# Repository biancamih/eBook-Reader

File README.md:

# OpenBook 
**Autor: Mihai Bianca-Ioana**

## Diagrama Bloc
```
                            +------------------------+
                            | USB-C Connector & ESD  |
                            +------------------------+
                                      |
                                      v
                             +------------------+
                             |   LDO Regulator   |
                             +------------------+
                                      |
                                      v
 +-------------------+       +------------------+       +---------------------+
 | Li-Po Charging IC | ----> | ESP32-C6 WROOM-1 | <-->  |    SD Card          |
 +-------------------+       +------------------+       +---------------------+
                                      |  ^   ^  ^
                                      |  |   |  |
         +------------------+         |  |   |  +---------------------+
         | Environmental     | -------+  |   +----------------+       |
         | Sensor (BME688)   |            |                    |       |
         +------------------+            |  +--------------+  |       |
                                         +->| NOR Flash     |<-+       |
                                         |  +--------------+          |
                                         |                             |
             +---------------+           +->| Battery Gauge |          |
             |   E-Paper     |<--------------+ (MAX17048)   |          |
             |   Driver      |           |  +---------------+          |
             +---------------+           |                             |
                                         +->| RTC (DS3231)  |<---------+
                                         |
                                         +->| Buttons       |
                                            +---------------+
```

## Bill Of  Materials (BOM)
| Component Name                            | Link                                                                                                   | Datasheet Link                                                                                           |
|------------------------------------------|-------------------------------------------------------------------------------------------------------------|-----------------------------------------------------------------------------------------------------------|
| 112ATAARR03ATTEND                        | [Link](https://store.comet.srl.ro/Catalogue/Product/43497/)                                                | [Link](https://www.attend.com.tw/data/download/file/112A-TAAR-R03.rar)                                   |
| ADAFRUIT_CHIP-LED0603                    | [Link](https://www.snapeda.com/parts/KP-1608SURCK/Kingbright/view-part/?ref=search&t=LED%200603)           | [Link](https://www.snapeda.com/parts/KP-1608SURCK/Kingbright/datasheet/)                                 |
| CAPCP3225X100N                           | [Link](https://www.snapeda.com/parts/CPH3225A/Seiko+Instruments/view-part/?ref=eda)                        | [Link](https://www.snapeda.com/parts/CPH3225A/Seiko%20Instruments/datasheet/)                            |
| DIOC1608X36N                             | [Link](https://www.snapeda.com/parts/PGB1010603MR/Littelfuse/view-part/?ref=eda)                           | [Link](https://www.snapeda.com/parts/PGB1010603MR/Littelfuse%20Inc./datasheet/)                          |
| EAGLE-LTSPICE_C0402                      | [Link](https://componentsearchengine.com/part-view/CC0402MRX5R5BB106/YAGEO)                                 | [Link](https://componentsearchengine.com/Datasheets/2/CC0402MRX5R5BB106.pdf)                              |
| ESP32_WROVER_AVX---SD0805S020S1R0_AVX_0  | [Link](https://ro.mouser.com/ProductDetail/KYOCERA-AVX/SD0805S020S1R0?qs=jCA%252BPfw4LHbpkAoSnwrdjw%3D%3D) | [Link](https://ro.mouser.com/datasheet/2/40/schottky-3165252.pdf)                                        |
| ESP32_WROVER_BME680_PSON80P300X300X100-8N| [Link](https://www.snapeda.com/parts/BME680/Bosch/view-part/?welcome=home)                                 | [Link](https://www.snapeda.com/parts/BME680/Bosch%20Sensortec/datasheet/)                                |
| ESP32_WROVER_EAGLE-LTSPICE_C0402         | [Link](https://componentsearchengine.com/part-view/CC0402MRX5R5BB106/YAGEO)                                 | [Link](https://componentsearchengine.com/Datasheets/2/CC0402MRX5R5BB106.pdf)                              |
| ESP32_WROVER_EAGLE-LTSPICE_R0402         | [Link](https://componentsearchengine.com/part-view/R0402%201%25%20100%20K%20(RC0402FR-07100KL)/YAGEO)       | [Link](https://www.yageo.com/upload/media/product/products/datasheet/rchip/PYu-RC_Group_51_RoHS_L_12.pdf)|
| ESP32_WROVER_SPARKFUN-DISCRETESEMI_SOT23-3| [Link](https://componentsearchengine.com/part-view/DMG2305UX-7/Diodes%20Incorporated)                      | [Link](https://www.diodes.com//assets/Datasheets/DMG2305UX.pdf)                                          |
| ESP32_WROVER_SPARKFUN-IC-POWER_SOT23-5   | [Link](https://ro.mouser.com/ProductDetail/Microchip-Technology/MCP73831T-5ACI-OT?qs=hH%252BOa0VZEiAcgAcEkuamXg%3D%3D) | [Link](https://ro.mouser.com/datasheet/2/268/MCP73831_Family_Data_Sheet_DS20001984H-3441711.pdf)         |
| ESP32C6_VARISTOR_CT/CN1812               | [Link](https://ro.mouser.com/ProductDetail/EPCOS-TDK/B72520T0350K062?qs=dEfas%2FXlABIszF52uu7vrg%3D%3D)     | [Link](https://www.tdk-electronics.tdk.com/inf/75/db/CTVS_14/Surge_protection_series.pdf)                |
| FH34SRJ24S05SH99                         | [Link](https://ro.mouser.com/ProductDetail/Hirose-Connector/FH34SRJ-24S-0.5SH99?qs=vcbW%252B4%252BSTIpKBl5ap9J8Fw%3D%3D) | [Link](https://ro.mouser.com/datasheet/2/185/FH34SRJ_24S_0_5SH_99__CL0580_1255_6_99_2DDrawing_0-1615044.pdf)|
| IND_4828-WE-TPC_WRE                      | [Link](https://ro.mouser.com/ProductDetail/Wurth-Elektronik/744043680?qs=PGXP4M47uW6VkZq%252BkzjrHA%3D%3D)  | [Link](https://www.we-online.com/components/products/datasheet/744043680.pdf)                            |
| JST04_1MM_RA                             | [Link](https://ro.mouser.com/ProductDetail/Adafruit/4208?qs=PzGy0jfpSMtbScLbr0L5dw%3D%3D)                   | [Link](https://ro.mouser.com/ProductDetail/Adafruit/4208?qs=PzGy0jfpSMtbScLbr0L5dw%3D%3D)                 |
| MYBUTTON                                 | [Link](https://industry.panasonic.com/global/en/products/control/switch/light-touch/number/evqpuj02k)      | [Link](https://industry.panasonic.com/global/en/downloads?tab=catalog&small_g_cd=203&part_no=EVQPUJ02K)  |
| RCL_CT3528                               | [Link](https://www.snapeda.com/parts/TAJB475K025RNJ/AVX/view-part/?t=capacitor%203528&con_ref=None)        | [Link](https://www.snapeda.com/parts/TAJB475K025RNJ/AVX/datasheet/)                                      |
| SAMACSYS_PARTS_USB4110GFA                | [Link](https://componentsearchengine.com/part-view/USB4110-GF-A/GCT%20(GLOBAL%20CONNECTOR%20TECHNOLOGY))   | [Link](https://gct.co/files/drawings/usb4110.pdf)                                                         |
| SOD3716X135N                             | [Link](https://ro.mouser.com/ProductDetail/KYOCERA-AVX/SD0805S020S1R0?qs=jCA%252BPfw4LHbpkAoSnwrdjw%3D%3D) | [Link](https://ro.mouser.com/datasheet/2/40/schottky-3165252.pdf)                                        |
| SOIC127P1032X265-16N                     | [Link](https://eu.mouser.com/ProductDetail/Wurth-Elektronik/744043680?qs=PGXP4M47uW6VkZq%252BkzjrHA%3D%3D)  | [Link](https://www.snapeda.com/parts/DS3231SN%23/Analog%20Devices/datasheet/)                            |
| SON127P600X800X80-9N                     | [Link](https://www.snapeda.com/parts/W25Q512JVEIQ/Winbond+Electronics/view-part/?ref=eda)                 | [Link](https://www.snapeda.com/parts/W25Q512JVEIQ/Winbond%20Electronics/datasheet/)                      |
| SON50P200X200X80-9N                      | [Link](https://www.snapeda.com/parts/MAX17048G+T10/Analog+Devices/view-part/?ref=eda)                      | [Link](https://www.snapeda.com/parts/MAX17048G+T10/Analog%20Devices/datasheet/)                          |
| SOT65P210X110-3N                         | [Link](https://componentsearchengine.com/part-view/SI1308EDL-T1-GE3/Vishay)                                 | [Link](https://componentsearchengine.com/Datasheets/1/SI1308EDL-T1-GE3.pdf)                               |
| SOT95P280X125-5N                         | [Link](https://componentsearchengine.com/part-view/BD5229G-TR/ROHM%20Semiconductor)                         | [Link](https://datasheet.datasheetarchive.com/originals/distributors/Datasheets_SAMA/f2b9741ef86007909f138d561a359946.pdf) |
| SOT95P280X145-6N                         | [Link](https://www.snapeda.com/parts/USBLC6-2SC6Y/STMicroelectronics/view-part/?ref=eda)                   | [Link](https://www.snapeda.com/parts/USBLC6-2SC6Y/STMicroelectronics/datasheet/)                         |
| XCVR_ESP32-C6-WROOM-1-N8                 | [Link](https://www.snapeda.com/parts/ESP32-C6-WROOM-1-N8/Espressif+Systems/view-part/?ref=eda)             | [Link](https://www.snapeda.com/parts/ESP32-C6-WROOM-1-N8/Espressif%20Systems/datasheet/)                 |

## Descriere functionala hardware 

###  Arhitectura Hardware

Sistemul este bazat pe microcontrollerul **ESP32-C6-WROOM-1**, cu conectivitate Wi-Fi 6 și BLE, gândit pentru funcționare autonomă și consum redus de energie. Dispozitivul este alimentat de la o baterie Li-Po și poate fi programat prin USB-C. Componentele sunt interconectate prin SPI, I2C și GPIO.

---

### Alimentare și management baterie

- **USB-C Connector & ESD Protection**  
  Conector: `USB4110-GF-A`  
  Protecție ESD: `USBLC6-2SC6Y`

- **LDO Voltage Regulator**  
  Asigură 3.3V stabil pentru întreaga placă

- **Li-Po Battery Charger**  
  MCP73831 – circuit dedicat pentru încărcarea bateriei

- **Battery Gauge (MAX17048)**  
  Măsoară nivelul bateriei și comunică prin I2C

---

### Microcontroller principal

- **ESP32-C6-WROOM-1-N8**  
  RISC-V MCU cu Wi-Fi 6, BLE, 8MB flash intern  
  Rol: control central, comunicare cu senzori, logare, afișare

---

### Stocare

- **SD Card** – pentru loguri de date, firmware, fișiere
- **W25Q512 NOR Flash** – pentru memorie suplimentară SPI (64Mbit)

---

### Senzori & Ceas

- **BME688** – măsoară temperatură, umiditate, presiune și gaze (I2C)
- **DS3231** – ceas de timp real, cu precizie ridicată (I2C)

---

### Afișaj

- **E-Paper Driver + Conector**  
  Conectat prin SPI, controlat de ESP32  
  Alimentarea este comutabilă cu un MOSFET (SI1308EDL)

---

### Control și testare

- **Reset / Boot Buttons**
- **Qwiic/Stemma QT Connector** – extensii I2C
- **Test Pads** – debugging ușor

---

### Protecții

- **TVS Diodes**: `PGB1010603MR` – protecție ESD pe linii sensibile
- **Varistori**: protecție la supratensiuni

---

### Conexiuni interfețe

| Interfață | Dispozitive conectate                          |
|-----------|------------------------------------------------|
| I2C       | BME688, DS3231, MAX17048                       |
| SPI       | SD Card, NOR Flash, E-Paper Display            |
| GPIO      | Butoane, LED-uri, Power switches               |

## Estimare Consum Energie

| Componentă                  | Mod activ (mA) | Standby (mA) | Deep sleep (µA) | Observații                                 |
|----------------------------|----------------|--------------|-----------------|--------------------------------------------|
| **ESP32-C6**               | 50–80          | ~2           | ~5              | Wi-Fi consumă cel mai mult                 |
| **BME688**                 | 2.1            | 0.15         | <1              | Măsurare la 1Hz                            |
| **DS3231 (RTC)**           | 0.15           | 0.15         | 0.15            | Activ permanent                            |
| **MAX17048 (Battery Gauge)**| 0.06          | 0.006        | 0.006           | Foarte eficient                            |
| **E-paper Display**        | 5–20           | 0            | 0               | Consumă doar în timpul refresh-ului        |
| **SD Card (scriere activă)**| 30–100        | 0.2          | 0               | Alimentat doar la nevoie                   |
| **W25Q512 (SPI Flash)**    | ~5             | 0.003        | <1              | Are mod standby foarte eficient            |
| **LDO Regulator + pierderi**| 2–5           | 0.5          | 0.2             | Inclus în consum general                   |

---

##  Mapare pini ESP32-C6 

| Pin ESP32-C6 | Componentă                     | Funcție/Interfață     | Motiv / Utilizare                                                                 |
|--------------|-------------------------------|------------------------|-----------------------------------------------------------------------------------|
| **IO0**      | Buton `BOOT`                  | GPIO / Input          | Intrare folosită pentru intrarea în mod bootloader                               |
| **IO1**      | `RTC DS3231`                  | I2C SDA               | Comunicare cu ceasul de timp real                                                |
| **IO2**      | `RTC DS3231`                  | I2C SCL               | Comunicare I2C                                                                    |
| **IO3**      | `BME688`, `MAX17048`          | I2C SDA               | Magistrală I2C partajată cu ceilalți senzori                                     |
| **IO4**      | `BME688`, `MAX17048`          | I2C SCL               |                                                                                   |
| **IO5**      | `W25Q512 NOR Flash`           | SPI CS                | Chip select pentru memoria flash externă                                         |
| **IO6**      | `W25Q512`, `SD Card`, `E-Paper`| SPI CLK               | Comun partajat între toate dispozitivele SPI                                     |
| **IO7**      | `W25Q512`, `SD Card`, `E-Paper`| SPI MISO              | Date de la dispozitive SPI                                                       |
| **IO8**      | `W25Q512`, `SD Card`, `E-Paper`| SPI MOSI              | Date către dispozitivele SPI                                                     |
| **IO9**      | `SD Card`                     | SPI CS                | Selectare card SD                                                                 |
| **IO10**     | `E-Paper`                     | SPI CS                | Selectare afișaj                                                                 |
| **IO11**     | `E-Paper`                     | BUSY / RESET / DC     | Control afișaj e-paper                                                            |
| **IO12**     | `E-Paper`                     | BUSY / RESET / DC     |                                                                                   |
| **IO13**     | `E-Paper`                     | BUSY / RESET / DC     |                                                                                   |
| **IO18**     | Buton `RESET`                 | GPIO / Input          | Reset hardware                                                                    |
| **IO19**     | LED / Control MOSFET-uri      | GPIO / Output         | Power gating sau status LED-uri                                                  |                                                |

## Observații și decizii de design:

- **SPI** este partajat între 3 periferice: SD card, NOR flash, e-paper. Fiecare are propriul pin CS.
- **I2C** este partajat între 3 dispozitive: BME688, DS3231 și MAX17048. Adresele sunt diferite.
- Pinul **IO0** este standard pentru BOOT, iar **IO18** este adesea folosit pentru RESET.
- GPIO suplimentare (ex. IO19, IO20) pot fi folosite pentru controlul alimentării modulelor (e.g., enable pin pe SD/e-paper).
- Se folosesc pinii **de jos (IO0–IO13)** pentru compatibilitate cu bootloader-ul și SPI flash extern.

## Randare PCB

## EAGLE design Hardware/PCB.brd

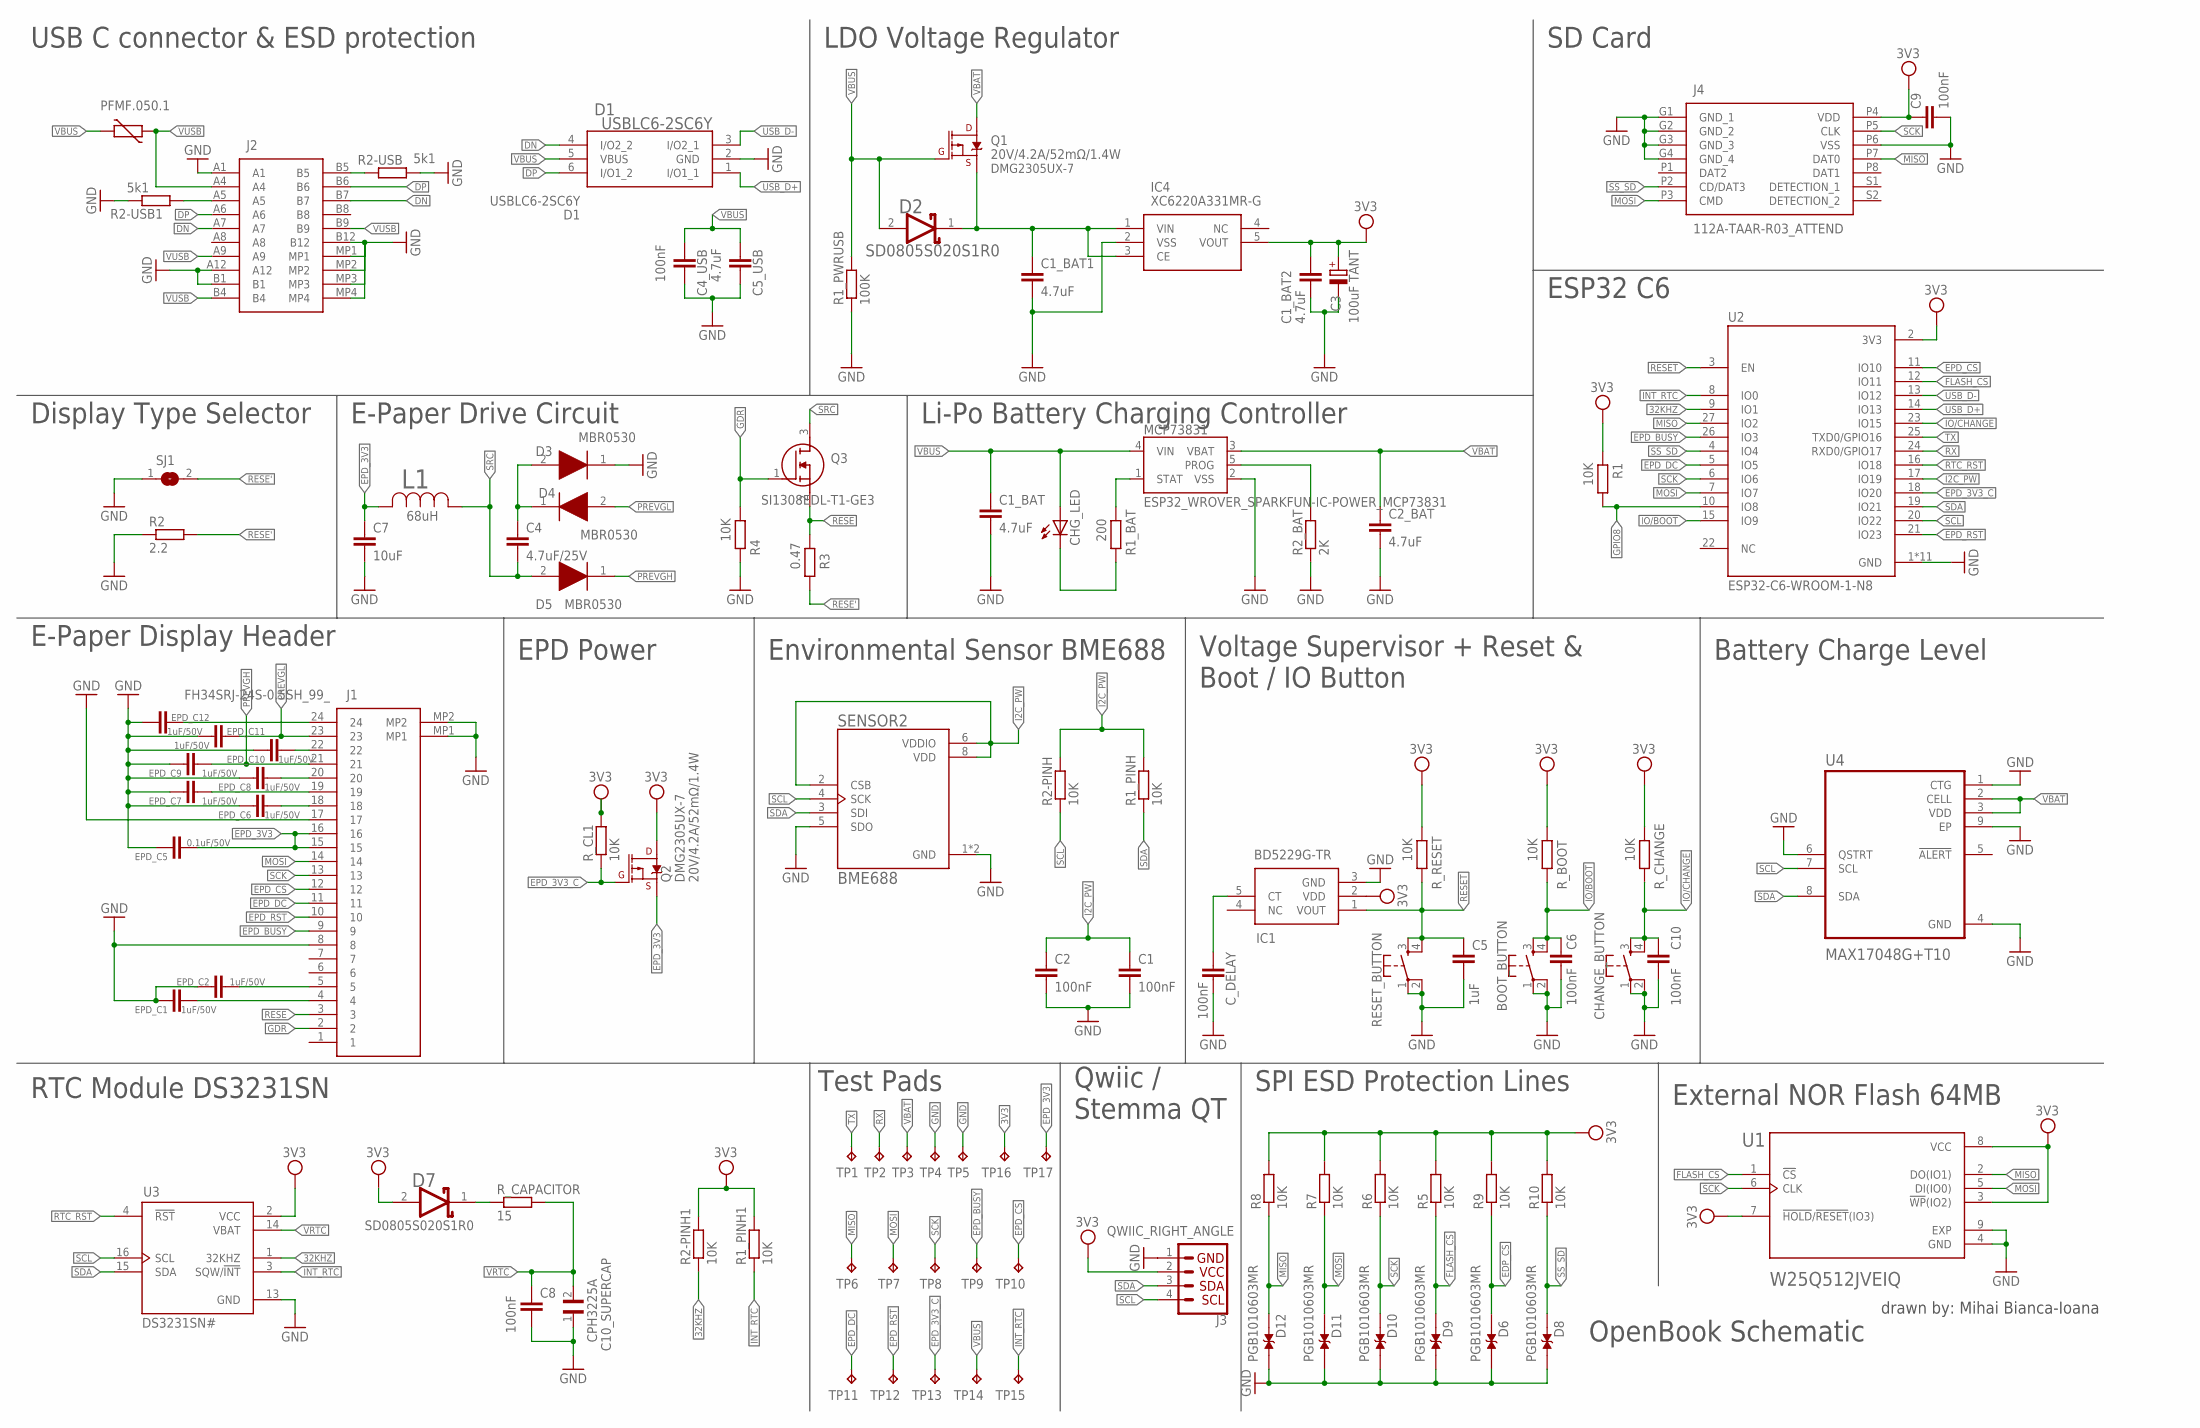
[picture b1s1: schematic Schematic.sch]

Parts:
BOOT_BUTTON: BUTTON_CUSYOMV1; MYBUTTON
C1, C2, C4_USB, C6, C8, C9, C10: 100nF; ESP32_WROVER_EAGLE-LTSPICE_C0402
C1_BAT, C2_BAT, C5_USB: 4.7uF; ESP32_WROVER_EAGLE-LTSPICE_C0402
C1_BAT1, C1_BAT2: 4.7uF; EAGLE-LTSPICE_C0402
C3: 100uF TANT; RCL_CT3528
C4: 4.7uF/25V; ESP32_WROVER_EAGLE-LTSPICE_C0402
C5: 1uF; ESP32_WROVER_EAGLE-LTSPICE_C0402
C7: 10uF; ESP32_WROVER_EAGLE-LTSPICE_C0402
C10_SUPERCAP: CPH3225A; CAPCP3225X100N
CHANGE_BUTTON: BUTTON_CUSYOMV1; MYBUTTON
CHG_LED: ADAFRUIT_LEDCHIP-LED0603; ADAFRUIT_CHIP-LED0603
C_DELAY: 100nF; ESP32_WROVER_EAGLE-LTSPICE_C0402
D1: USBLC6-2SC6Y; SOT95P280X145-6N
D2, D7: ESP32_WROVER_AVX---SD0805S020S1R0_AVX_SD0805S020S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; ESP32_WROVER_AVX---SD0805S020S1R0_AVX_SD0805S020S1R0_0
D3, D4, D5: MBR0530; SOD3716X135N
D6, D8, D9, D10, D11, D12: PGB1010603MR; DIOC1608X36N
EPD_C1, EPD_C2, EPD_C6, EPD_C7, EPD_C8, EPD_C9, EPD_C10, EPD_C11, EPD_C12: 1uF/50V; ESP32_WROVER_EAGLE-LTSPICE_C0402
EPD_C5: 0.1uF/50V; ESP32_WROVER_EAGLE-LTSPICE_C0402
IC1: BD5229G-TR; SOT95P280X125-5N
IC4: XC6220A331MR-G; SOT95P280X120-5N
J1: FH34SRJ-24S-0.5SH_99_; FH34SRJ24S05SH99
J2: SAMACSYS_PARTS_USB4110-GF-A; SAMACSYS_PARTS_USB4110GFA
J3: QWIIC_RIGHT_ANGLE; JST04_1MM_RA
J4: 112A-TAAR-R03_ATTEND; 112ATAARR03ATTEND
L1: 68uH; IND_4828-WE-TPC_WRE
MCP73831: ESP32_WROVER_SPARKFUN-IC-POWER_MCP73831; ESP32_WROVER_SPARKFUN-IC-POWER_SOT23-5
PFMF.050.1: ESP32C6_VARISTORCN1812; ESP32C6_VARISTOR_CT/CN1812
Q1, Q2: 20V/4.2A/52mΩ/1.4W; ESP32_WROVER_SPARKFUN-DISCRETESEMI_SOT23-3
Q3: SI1308EDL-T1-GE3; SOT65P210X110-3N
R1, R1_PINH, R1_PINH1, R2-PINH, R2-PINH1, R4, R5, R6, R7, R8, R9, R10: 10K; ESP32_WROVER_EAGLE-LTSPICE_R0402
R1_BAT: 200; ESP32_WROVER_EAGLE-LTSPICE_R0402
R1_PWRUSB: 100K; ESP32_WROVER_EAGLE-LTSPICE_R0402
R2: 2.2; ESP32_WROVER_EAGLE-LTSPICE_R0402
R2-USB, R2-USB1: 5k1; ESP32_WROVER_EAGLE-LTSPICE_R0402
R2_BAT: 2K; ESP32_WROVER_EAGLE-LTSPICE_R0402
R3: 0.47; ESP32_WROVER_EAGLE-LTSPICE_R0402
RESET_BUTTON: BUTTON_CUSYOMV1; MYBUTTON
R_BOOT: 10K; ESP32_WROVER_EAGLE-LTSPICE_R0402
R_CAPACITOR: 15; ESP32_WROVER_EAGLE-LTSPICE_R0402
R_CHANGE: 10K; ESP32_WROVER_EAGLE-LTSPICE_R0402
R_CL1: 10K; ESP32_WROVER_EAGLE-LTSPICE_R0402
R_RESET: 10K; ESP32_WROVER_EAGLE-LTSPICE_R0402
SENSOR2: BME688; ESP32_WROVER_BME680_PSON80P300X300X100-8N
SJ1: SJ
TP1, TP2, TP3, TP4, TP5, TP6, TP7, TP8, TP9, TP10, TP11, TP12, TP13, TP14, TP15, TP16, TP17: TPTP20R; TP20R
U1: W25Q512JVEIQ; SON127P600X800X80-9N
U2: ESP32-C6-WROOM-1-N8; XCVR_ESP32-C6-WROOM-1-N8
U3: DS3231SN#; SOIC127P1032X265-16N
U4: MAX17048G+T10; SON50P200X200X80-9N

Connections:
3V3: C1_BAT2.1, C3.+, C9.1, D7.2 (ANODE), IC1.2 (VDD), IC4.5 (VOUT), J3.2, J4.P4 (VDD), Q2.3 (D), R1.2, R1_PINH1.2, R2-PINH1.2, R5.2, R6.2, R7.2, R8.2, R9.2, R10.2, R_BOOT.2, R_CHANGE.2, R_CL1.2, R_RESET.2, TP16.TP, U1.3 (!WP!(IO2)), U1.7 (!HOLD!/!RESET!(IO3)), U1.8 (VCC), U2.2 (3V3), U3.2 (VCC)
32KHZ: R2-PINH1.1, U2.9 (IO1), U3.1 (32KHZ)
DN: D1.4 (I/O2_2), J2.A7, J2.B7
DP: D1.6 (I/O1_2), J2.A6, J2.B6
EDP_CS: D6.1, R9.1
EPD_3V3: C7.1, EPD_C5.2, J1.15, J1.16, L1.2, Q2.2 (S), TP17.TP
EPD_3V3_C: Q2.1 (G), R_CL1.1, TP13.TP, U2.18 (IO20)
EPD_BUSY: J1.9, TP9.TP, U2.26 (IO3)
EPD_CS: J1.12, TP10.TP, U2.11 (IO10)
EPD_DC: J1.11, TP11.TP, U2.5 (IO5)
EPD_RST: J1.10, TP12.TP, U2.21 (IO23)
FLASH_CS: D9.1, R5.1, U1.1 (!CS), U2.12 (IO11)
GDR: J1.2, Q3.1 (G), R4.2
GND: BOOT_BUTTON.1, BOOT_BUTTON.2, C1.2, C1_BAT.2, C1_BAT1.2, C1_BAT2.2, C2.2, C2_BAT.2, C3.-, C4_USB.2, C5.2, C5_USB.2, C6.2, C7.2, C8.2, C9.2, C10.2, C10_SUPERCAP.1, CHANGE_BUTTON.1, CHANGE_BUTTON.2, C_DELAY.2, D1.2 (GND), D3.1 (K), D6.2, D8.2, D9.2, D10.2, D11.2, D12.2, EPD_C1.1, EPD_C2.1, EPD_C5.1, EPD_C6.1, EPD_C7.1, EPD_C8.1, EPD_C9.1, EPD_C10.1, EPD_C11.1, EPD_C12.1, IC1.3 (GND), IC4.2 (VSS), J1.8, J1.17, J1.MP1, J1.MP2, J2.A1, J2.A12, J2.B1, J2.B12, J2.MP1, J2.MP2, J2.MP3, J2.MP4, J3.1, J4.G1 (GND_1), J4.G2 (GND_2), J4.G3 (GND_3), J4.G4 (GND_4), J4.P6 (VSS), MCP73831.2 (VSS), R1_PWRUSB.1, R2.1, R2-USB.2, R2-USB1.2, R2_BAT.1, R4.1, RESET_BUTTON.1, RESET_BUTTON.2, SENSOR2.1 (GND), SENSOR2.5 (SDO), SENSOR2.7 (GND), SJ1.1, TP4.TP, TP5.TP, U1.4 (GND), U1.9 (EXP), U2.1 (GND), U2.28 (GND), U2.29_1 (GND), U2.29_2 (GND), U2.29_3 (GND), U2.29_4 (GND), U2.29_5 (GND), U2.29_6 (GND), U2.29_7 (GND), U2.29_8 (GND), U2.29_9 (GND), U3.13 (GND), U4.1 (CTG), U4.4 (GND), U4.6 (QSTRT), U4.9 (EP)
GPIO8: R1.1, U2.10 (IO8)
I2C_PW: C1.1, C2.1, R1_PINH.2, R2-PINH.2, SENSOR2.2 (CSB), SENSOR2.6 (VDDIO), SENSOR2.8 (VDD), U2.17 (IO19)
INT_RTC: R1_PINH1.1, TP15.TP, U2.8 (IO0), U3.3 (SQW/!INT)
IO/BOOT: BOOT_BUTTON.3, BOOT_BUTTON.4, C6.1, R_BOOT.1, U2.15 (IO9)
IO/CHANGE: C10.1, CHANGE_BUTTON.3, CHANGE_BUTTON.4, R_CHANGE.1, U2.23 (IO15)
MISO: D12.1, J4.P7 (DAT0), R8.1, TP6.TP, U1.2 (DO(IO1)), U2.27 (IO2)
MOSI: D11.1, J1.14, J4.P3 (CMD), R7.1, TP7.TP, U1.5 (DI(IO0)), U2.7 (IO7)
unnamed: J2.A5, R2-USB1.1
unnamed: J2.B5, R2-USB.1
unnamed: C1_BAT1.1, D2.1 (CATHODE), IC4.1 (VIN), IC4.3 (CE), Q1.2 (S)
unnamed: D7.1 (CATHODE), R_CAPACITOR.1
unnamed: C_DELAY.1, IC1.5 (CT)
unnamed: MCP73831.1 (STAT), R1_BAT.2
unnamed: C4.1, D3.2 (A), D4.1 (K)
unnamed: CHG_LED.C, R1_BAT.1
unnamed: EPD_C12.2, J1.24
unnamed: EPD_C10.2, J1.22
unnamed: EPD_C8.2, J1.20
unnamed: EPD_C7.2, J1.19
unnamed: EPD_C6.2, J1.18
unnamed: MCP73831.5 (PROG), R2_BAT.2
unnamed: EPD_C1.2, J1.4
unnamed: EPD_C2.2, J1.5
PREVGH: D5.1 (K), EPD_C9.2, J1.21
PREVGL: D4.2 (A), EPD_C11.2, J1.23
RESE: J1.3, Q3.2 (S), R3.2
RESE': R2.2, R3.1, SJ1.2
RESET: C5.1, IC1.1 (VOUT), RESET_BUTTON.3, RESET_BUTTON.4, R_RESET.1, U2.3 (EN)
RTC_RST: U2.16 (IO18), U3.4 (!RST)
RX: TP2.TP, U2.24 (RXD0/GPIO17)
SCK: D10.1, J1.13, J4.P5 (CLK), R6.1, TP8.TP, U1.6 (CLK), U2.6 (IO6)
SCL: J3.4, R2-PINH.1, SENSOR2.4 (SCK), U2.20 (IO22), U3.16 (SCL), U4.7 (SCL)
SDA: J3.3, R1_PINH.1, SENSOR2.3 (SDI), U2.19 (IO21), U3.15 (SDA), U4.8 (SDA)
SRC: C4.2, D5.2 (A), L1.1, Q3.3 (D)
SS_SD: D8.1, J4.P2 (CD/DAT3), R10.1, U2.4 (IO4)
TX: TP1.TP, U2.25 (TXD0/GPIO16)
USB_D+: D1.1 (I/O1_1), U2.14 (IO13)
USB_D-: D1.3 (I/O2_1), U2.13 (IO12)
VBAT: C2_BAT.1, MCP73831.3 (VBAT), Q1.3 (D), TP3.TP, U4.2 (CELL), U4.3 (VDD)
VBUS: C1_BAT.1, C4_USB.1, C5_USB.1, CHG_LED.A, D1.5 (VBUS), D2.2 (ANODE), MCP73831.4 (VIN), PFMF.050.1.2, Q1.1 (G), R1_PWRUSB.2, TP14.TP
VRTC: C8.1, C10_SUPERCAP.2, R_CAPACITOR.2, U3.14 (VBAT)
VUSB: J2.A4, J2.A9, J2.B4, J2.B9, PFMF.050.1.1

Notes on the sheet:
USB C connector & ESD protection
LDO Voltage Regulator
SD Card
ESP32 C6
Battery Charge Level
External NOR Flash 64MB
SPI ESD Protection Lines
Qwiic / Stemma QT
Test Pads
RTC Module DS3231SN
E-Paper Display Header
EPD Power
Environmental Sensor BME688
Voltage Supervisor + Reset & Boot / IO Button
Display Type Selector
E-Paper Drive Circuit
Li-Po Battery Charging Controller
OpenBook Schematic
drawn by: Mihai Bianca-Ioana

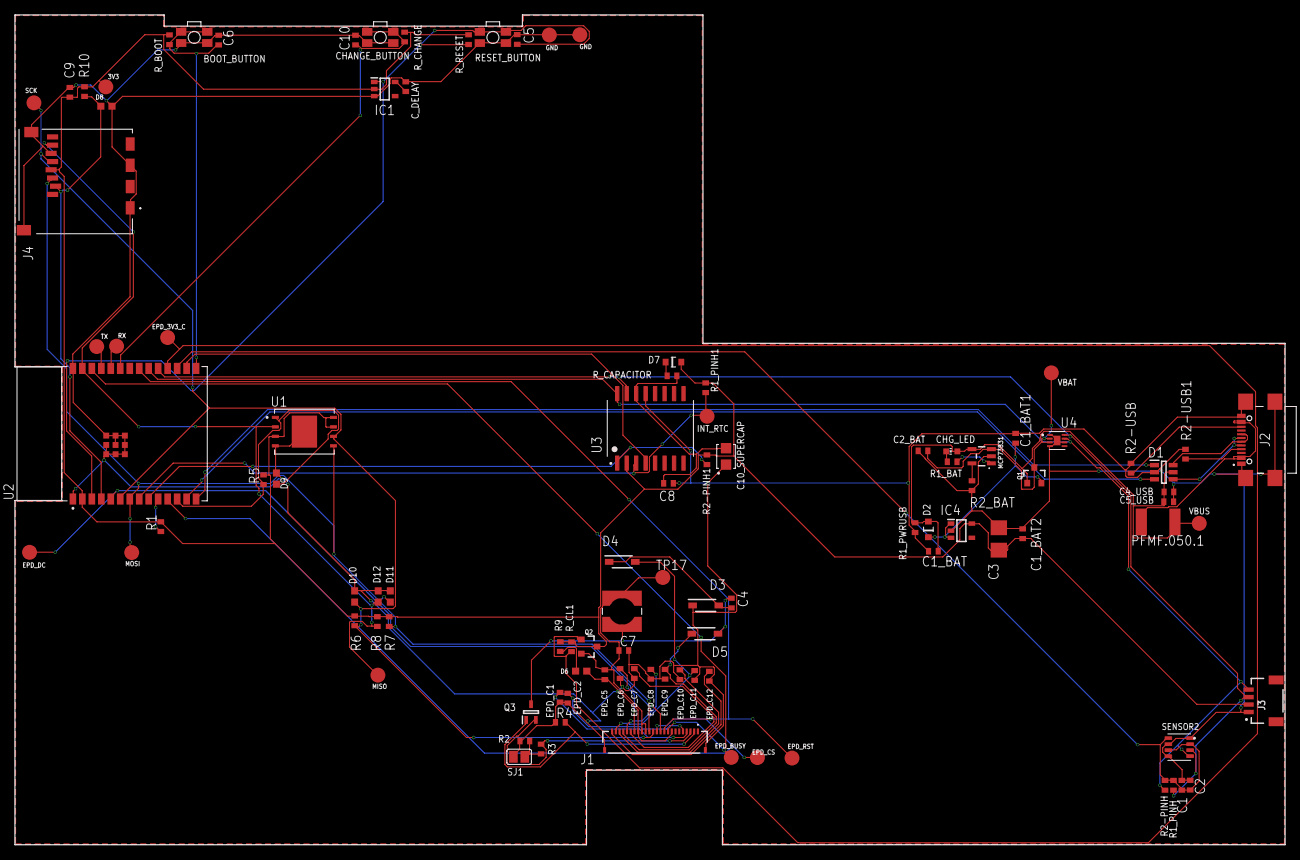
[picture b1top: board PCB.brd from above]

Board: 2 copper layers, 170.2 x 111.2 mm, 103 parts (0 on the bottom side), 56 nets.

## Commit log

2025-04-06 upload
2025-04-06 Create LICENSE
2025-04-13 Solved issues

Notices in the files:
parts and their libraries:
COPYRIGHT: Copyright (C) 2024 Ultra Librarian. All rights reserved.
